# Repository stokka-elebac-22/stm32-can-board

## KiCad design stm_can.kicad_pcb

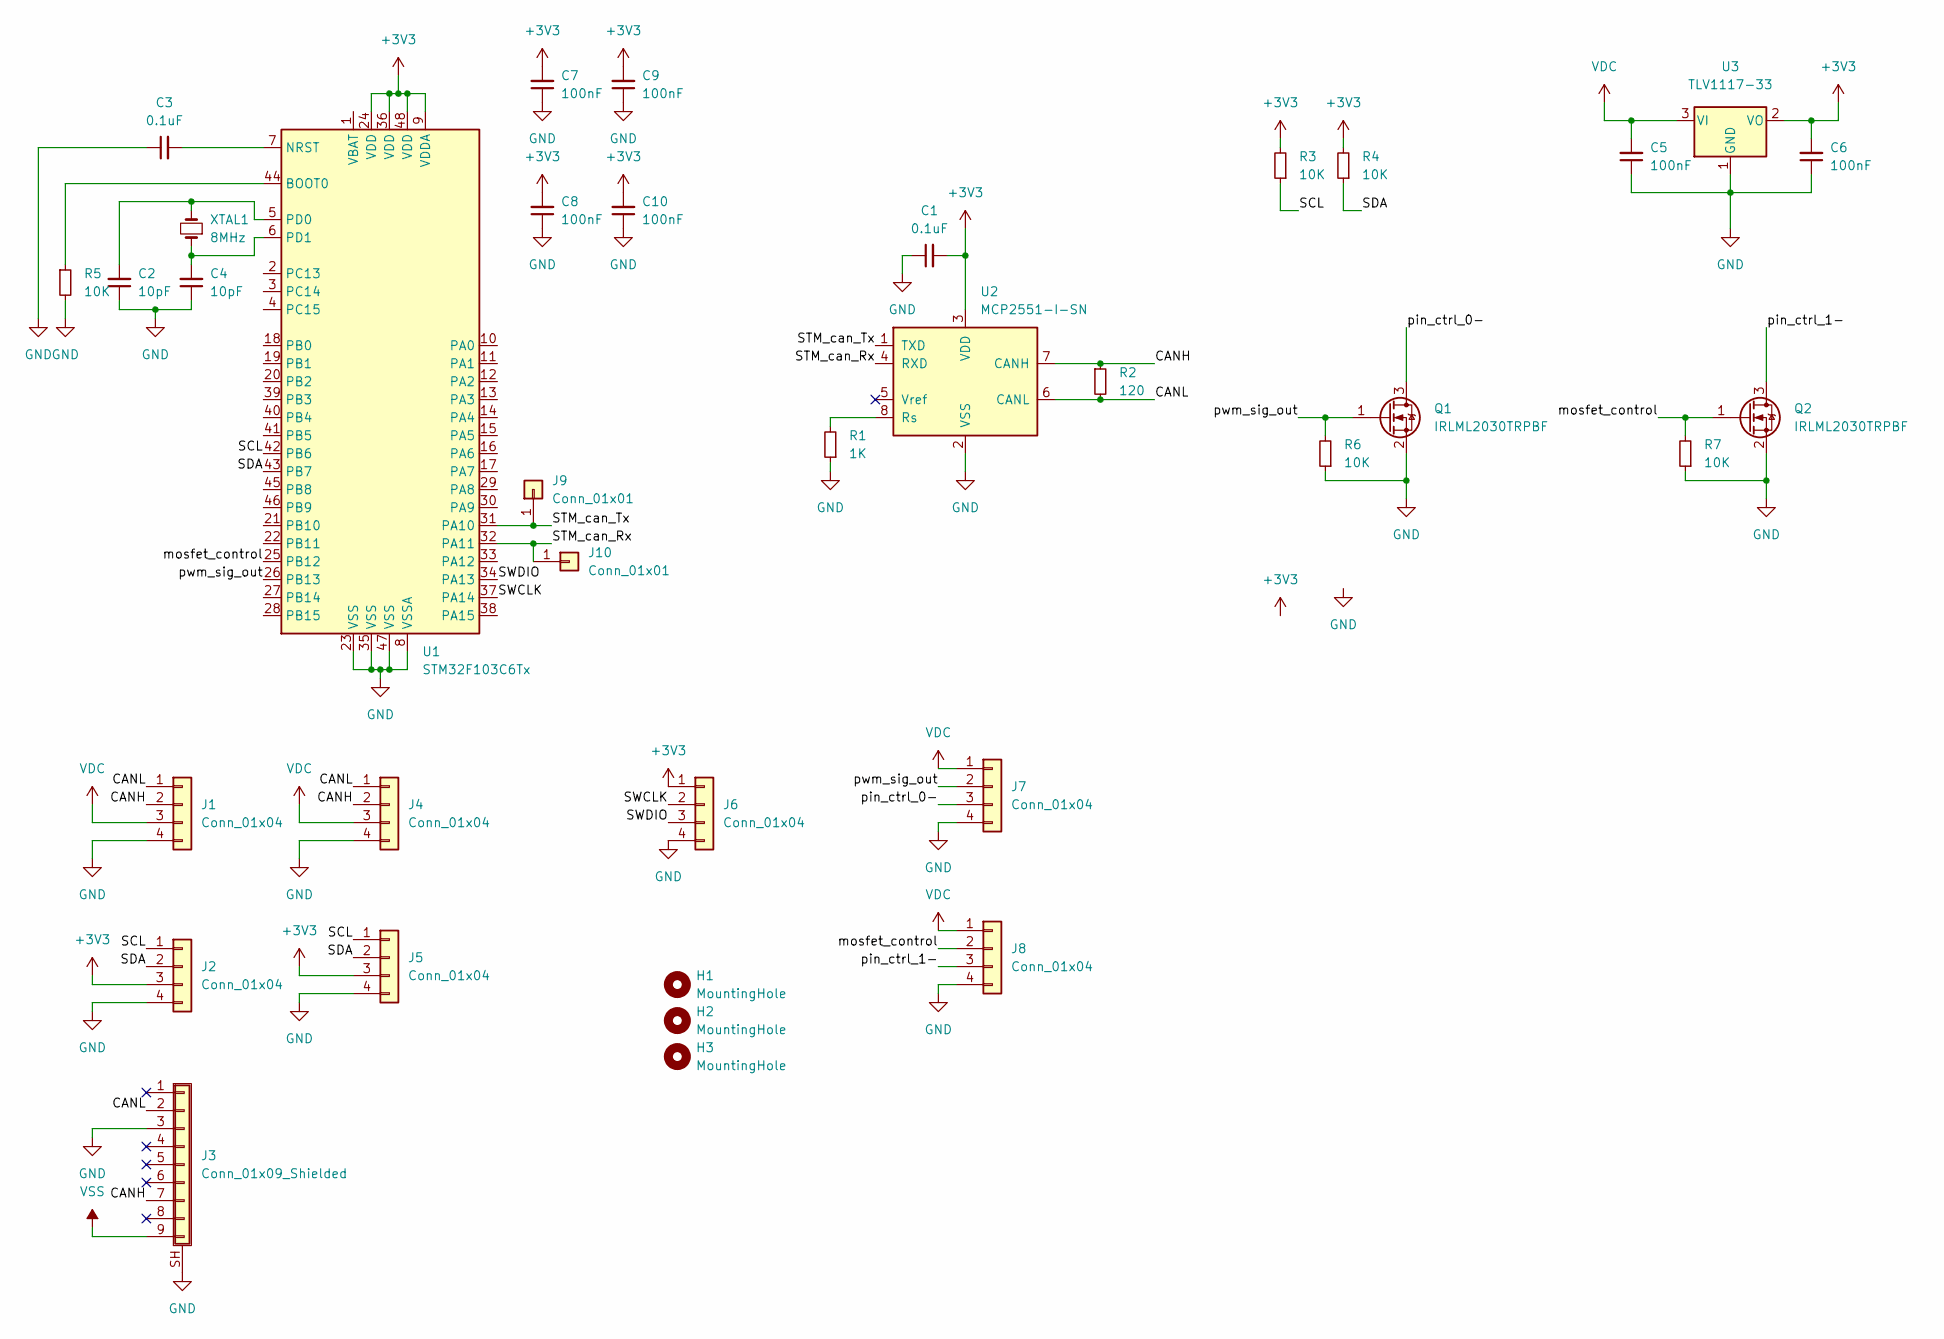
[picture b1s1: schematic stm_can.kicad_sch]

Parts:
C1, C3: 0.1uF; C_0805_2012Metric_Pad1.18x1.45mm_HandSolder
C2, C4: 10pF; C_0805_2012Metric_Pad1.18x1.45mm_HandSolder
C5, C6, C7, C8, C9, C10: 100nF; C_0805_2012Metric_Pad1.18x1.45mm_HandSolder
H1, H2, H3: MountingHole; MountingHole_3.2mm_M3
J1, J4: Conn_01x04; JST_XH_S4B-XH-A-1_1x04_P2.50mm_Horizontal-SMD
J2, J5, J7, J8: Conn_01x04; Molex_PicoBlade_53398-0471_1x04-1MP_P1.25mm_Vertical
J3: Conn_01x09_Shielded; DSUB-9_Female_Horizontal_P2.77x2.84mm_EdgePinOffset4.94mm_H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
J6: Conn_01x04; PinHeader_1x04_P1.27mm_Vertical
J9, J10: Conn_01x01; PinHeader_1x01_P1.27mm_Vertical
Q1, Q2: IRLML2030TRPBF; SOT-23
R1: 1K; R_0805_2012Metric_Pad1.20x1.40mm_HandSolder
R2: 120; R_0805_2012Metric_Pad1.20x1.40mm_HandSolder
R3, R4, R5, R6, R7: 10K; R_0805_2012Metric_Pad1.20x1.40mm_HandSolder
U1: STM32F103C6Tx; LQFP-48_7x7mm_P0.5mm
U2: MCP2551-I-SN; SOIC-8_3.9x4.9mm_P1.27mm
U3: TLV1117-33; SOT-223
XTAL1: 8MHz; Crystal_SMD_8mhz_HandSoldering

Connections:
+3V3: C1.2, C6.2, C7.2, C8.2, C9.2, C10.2, J2.3, J5.3, J6.1, R3.2, R4.2, U1.9 (VDDA), U1.24 (VDD), U1.36 (VDD), U1.48 (VDD), U2.3 (VDD), U3.2 (VO)
/CANH: J1.2, J3.7, J4.2, R2.1, U2.7 (CANH)
/CANL: J1.1, J3.2, J4.1, R2.2, U2.6 (CANL)
/SCL: J2.1, J5.1, R3.1, U1.42 (PB6)
/SDA: J2.2, J5.2, R4.1, U1.43 (PB7)
/STM_can_Rx: J10.1, U1.32 (PA11), U2.4 (RXD)
/STM_can_Tx: J9.1, U1.31 (PA10), U2.1 (TXD)
/SWCLK: J6.2, U1.37 (PA14)
/SWDIO: J6.3, U1.34 (PA13)
/mosfet_control: J8.2, Q2.1 (G), R7.2, U1.25 (PB12)
/pin_ctrl_0-: J7.3, Q1.3 (D)
/pin_ctrl_1-: J8.3, Q2.3 (D)
/pwm_sig_out: J7.2, Q1.1 (G), R6.2, U1.26 (PB13)
GND: C1.1, C2.1, C3.1, C4.1, C5.1, C6.1, C7.1, C8.1, C9.1, C10.1, J1.4, J2.4, J3.3, J3.SH (Shield), J4.4, J5.4, J6.4, J7.4, J8.4, Q1.2 (S), Q2.2 (S), R1.1, R5.2, R6.1, R7.1, U1.8 (VSSA), U1.23 (VSS), U1.35 (VSS), U1.47 (VSS), U2.2 (VSS), U3.1 (GND)
unnamed: R1.2, U2.8 (Rs)
unnamed 15: C2.2, U1.5 (PD0), XTAL1.2; also elsewhere on the board
unnamed 16: C4.2, U1.6 (PD1), XTAL1.1; also elsewhere on the board
unnamed: C3.2, U1.7 (NRST)
unnamed: R5.1, U1.44 (BOOT0)
VDC: C5.2, J1.3, J4.3, J7.1, J8.1, U3.3 (VI)
VSS: J3.9

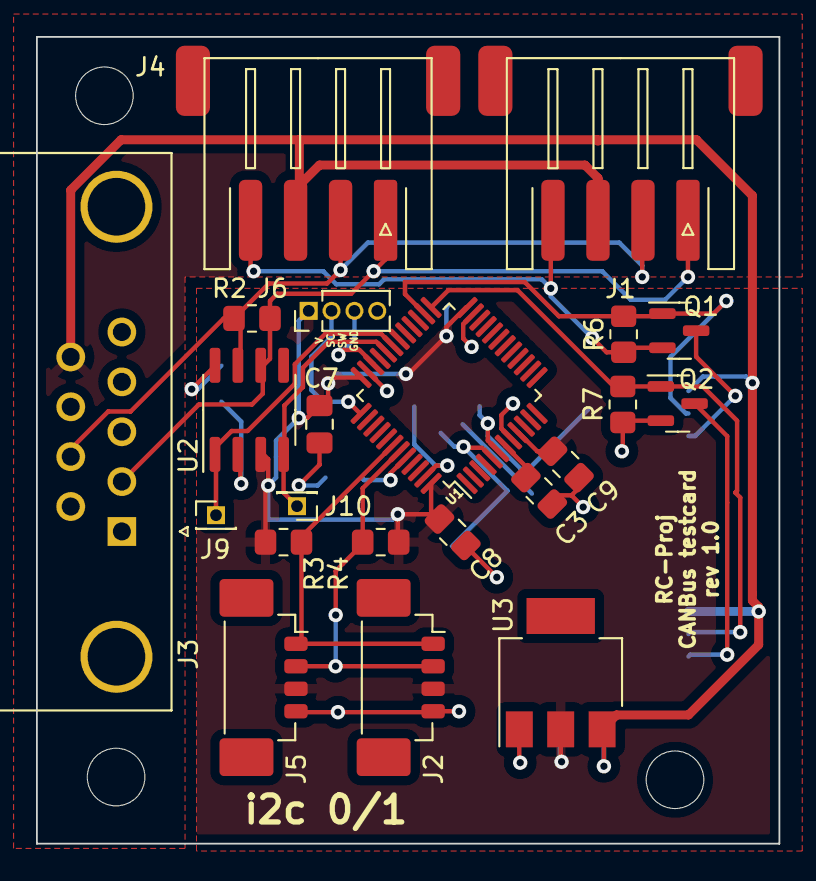
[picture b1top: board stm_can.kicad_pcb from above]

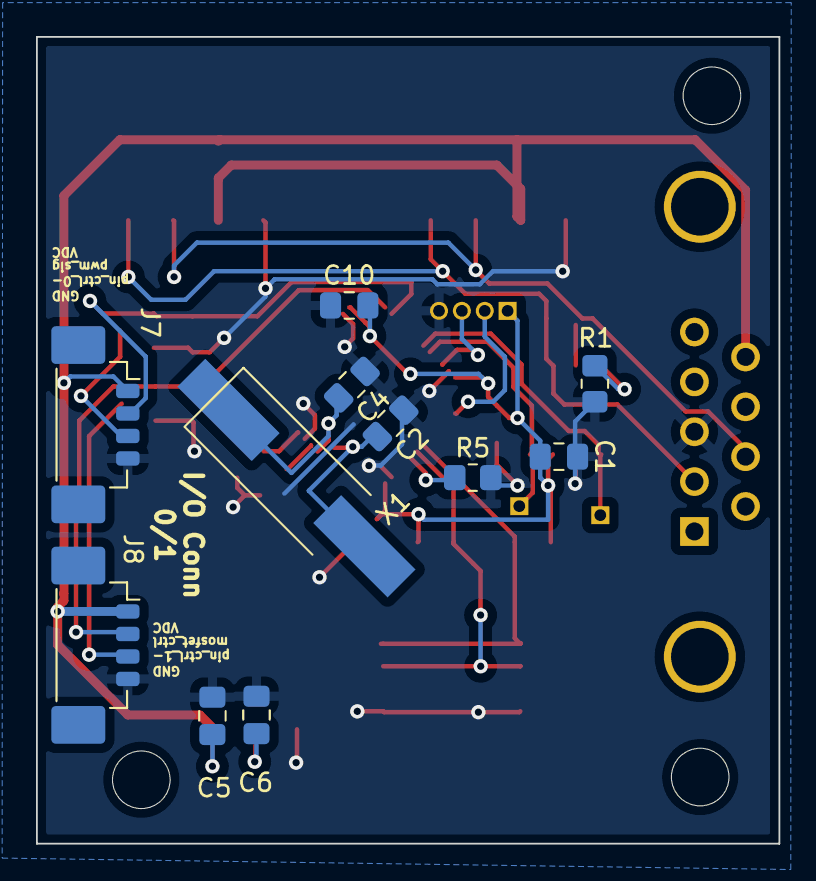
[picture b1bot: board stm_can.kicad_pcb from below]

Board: 2 copper layers, 41.2 x 44.8 mm, 36 parts (11 on the bottom side), 20 nets.

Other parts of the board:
X1: 8MHz; Crystal_SMD_8mhz_HandSoldering

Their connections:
unnamed 15: X1.2; also elsewhere on the board
unnamed 16: X1.1; also elsewhere on the board

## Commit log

2022-12-15 Rev 1.0
    Broken design!
